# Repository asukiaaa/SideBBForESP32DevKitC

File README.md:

# SideBBForESP32DevKitC

A project to extend pins from ESP32DevKitC to arround a mini bread board.

Run the following command to use submodule.
```
git submodule update --init
```

## Where to buy

[SideBBForESP32DevKitC - スイッチサイエンス](https://www.switch-science.com/catalog/8071/)

## License

MIT

## References

- [製品紹介 SideBB For ESP32DevKitC](https://asukiaaa.blogspot.com/2022/04/SideBBForESP32DevKitC.html)

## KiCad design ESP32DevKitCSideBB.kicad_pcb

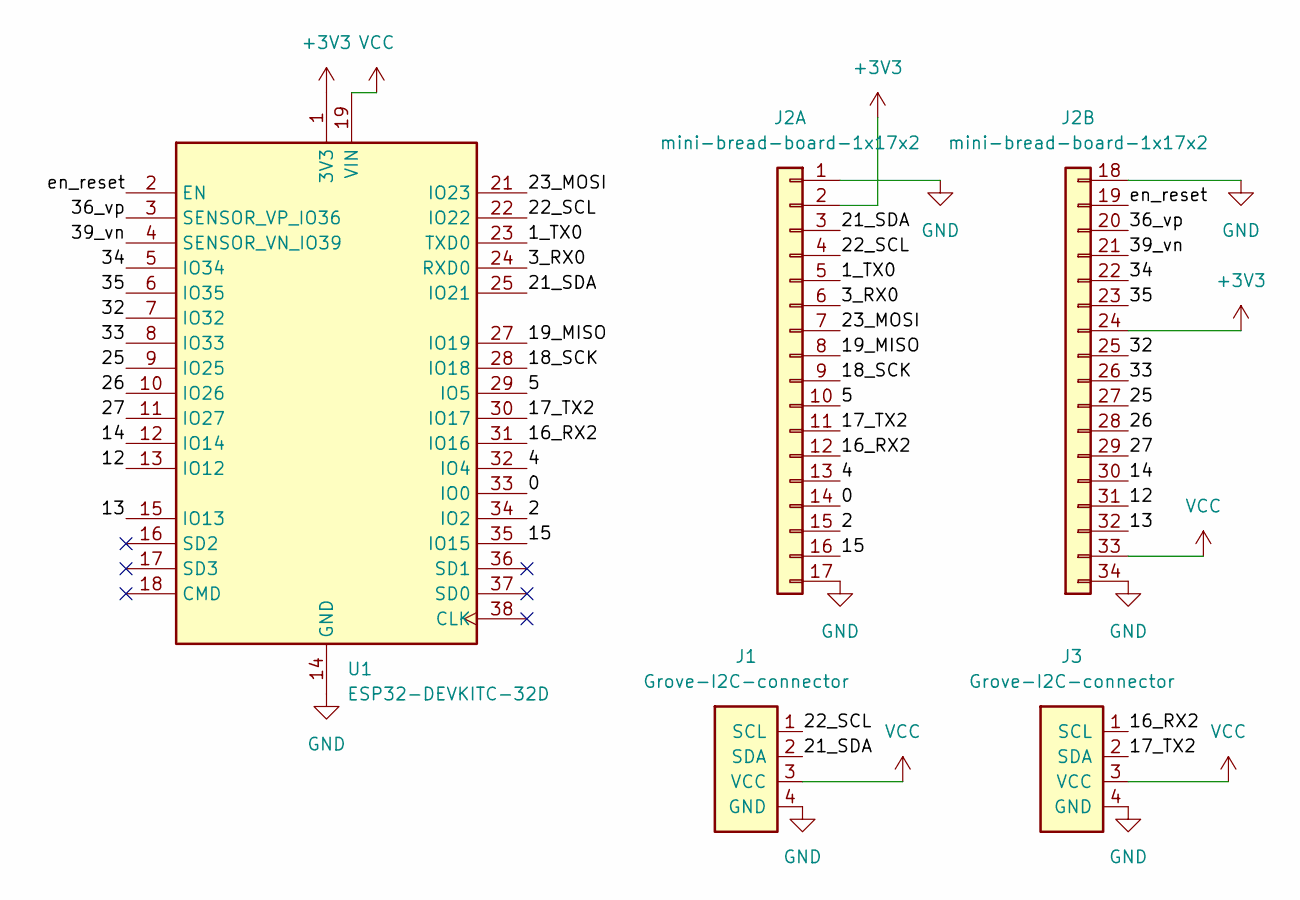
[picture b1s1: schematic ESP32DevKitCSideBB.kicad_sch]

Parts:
J1, J3: Grove-I2C-connector; NS-Tech_Grove_1x04_P2mm_Vertical
J2: mini-bread-board-1x17x2
U1: ESP32-DEVKITC-32D

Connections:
+3V3: J2.2 (Pin_19), J2.24, U1.1 (3V3)
/0: J2.14 (Pin_31), U1.33 (IO0)
/1_TX0: J2.5 (Pin_22), U1.23 (TXD0)
/2: J2.15 (Pin_32), U1.34 (IO2)
/3_RX0: J2.6 (Pin_23), U1.24 (RXD0)
/4: J2.13 (Pin_30), U1.32 (IO4)
/5: J2.10 (Pin_27), U1.29 (IO5)
/12: J2.31, U1.13 (IO12)
/13: J2.32, U1.15 (IO13)
/14: J2.30, U1.12 (IO14)
/15: J2.16 (Pin_33), U1.35 (IO15)
/16_RX2: J2.12 (Pin_29), J3.1 (SCL), U1.31 (IO16)
/17_TX2: J2.11 (Pin_28), J3.2 (SDA), U1.30 (IO17)
/18_SCK: J2.9 (Pin_26), U1.28 (IO18)
/19_MISO: J2.8 (Pin_25), U1.27 (IO19)
/21_SDA: J1.2 (SDA), J2.3 (Pin_20), U1.25 (IO21)
/22_SCL: J1.1 (SCL), J2.4 (Pin_21), U1.22 (IO22)
/23_MOSI: J2.7 (Pin_24), U1.21 (IO23)
/25: J2.27, U1.9 (IO25)
/26: J2.28, U1.10 (IO26)
/27: J2.29, U1.11 (IO27)
/32: J2.25, U1.7 (IO32)
/33: J2.26, U1.8 (IO33)
/34: J2.22, U1.5 (IO34)
/35: J2.23, U1.6 (IO35)
/36_vp: J2.20, U1.3 (SENSOR_VP_IO36)
/39_vn: J2.21, U1.4 (SENSOR_VN_IO39)
/en_reset: J2.19, U1.2 (EN)
GND: J1.4 (GND), J2.1 (Pin_18), J2.17 (Pin_34), J2.18, J2.34, J3.4 (GND), U1.14 (GND), U1.20 (GND), U1.26 (GND)
VCC: J1.3 (VCC), J2.33, J3.3 (VCC), U1.19 (VIN)

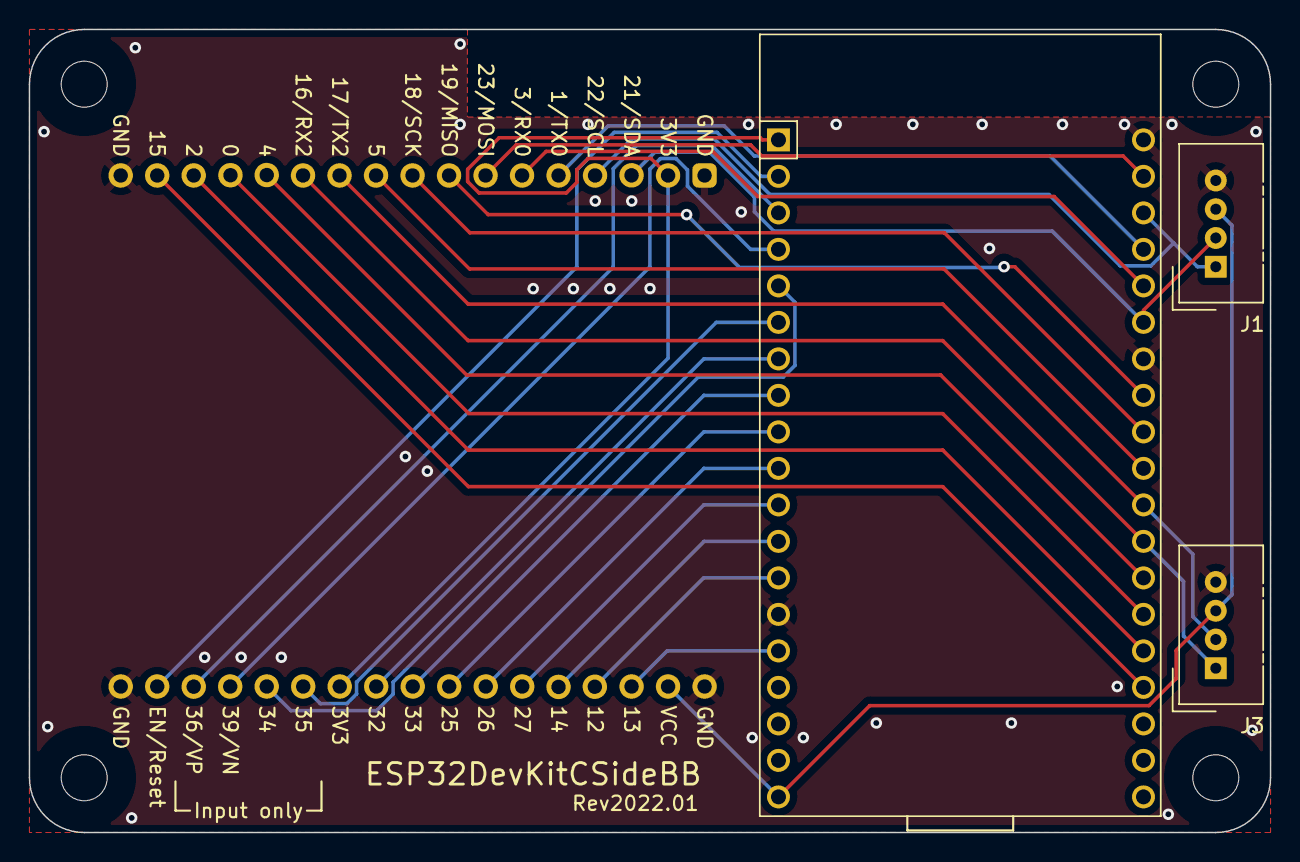
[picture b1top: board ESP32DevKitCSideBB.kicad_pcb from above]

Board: 2 copper layers, 86.4 x 55.9 mm, 8 parts (0 on the bottom side), 30 nets.

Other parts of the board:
REF1, REF2, REF3, REF4: MountingHole_3.2mm_M3

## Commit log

2022-01-28 Rename project name as ESP32DevKitCSideBB
2022-02-13 Rename project name to SideBBForESP32DevKitC
2022-02-13 Ignore gerber_to_order directory
2022-02-13 Add explanation of this board on readme
2022-03-02 Correct url for asukiaaa-kicad libs
2022-03-21 Correct pad for mini bread board
2022-04-17 Add command to init submodule
2022-04-17 Add link of my blog to readme
2022-04-17 Add license info as MIT
2022-04-17 Add schema pdf
2022-04-23 Add link of switch science web store on readme
2022-04-23 Add comment to open file with using KiCad on readme
2022-04-30 Remove mask for mounting holes and move gnd label position
2022-04-30 Add bom
